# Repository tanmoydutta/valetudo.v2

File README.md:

# Valetudo V2 - a CR2032 powered Temperature and Humidity sensor with ePaper display
Valetudo V2 has been an improvement on the previous version to add an onboard SEN40 Temperature / Humidity Sensor. This design also includes adjustments to the Battery circuit as well as support for different variants of the ePaper Display.

The form factor has remained the same for the new PCB and some of the components have been slightly reoriented to make room for the new electronics. Powered by the same CR2032 coin cell with firmware enhancements to improve battery life.

The body and the lid of the enclosure are embedded with magnetic snap-on feature with an acrylic viewing window for protection for the epaper display. 

The enclosure is now fitted with two large 12x3 mm neodymium magnets for better strength to remain stuck with a metallic surface like a refrigerator or a whiteboard.

This project is certified as Open Source Hardware - 
<p align="center">
  
</p>

License information on the hardware and software and documentation is as follows -

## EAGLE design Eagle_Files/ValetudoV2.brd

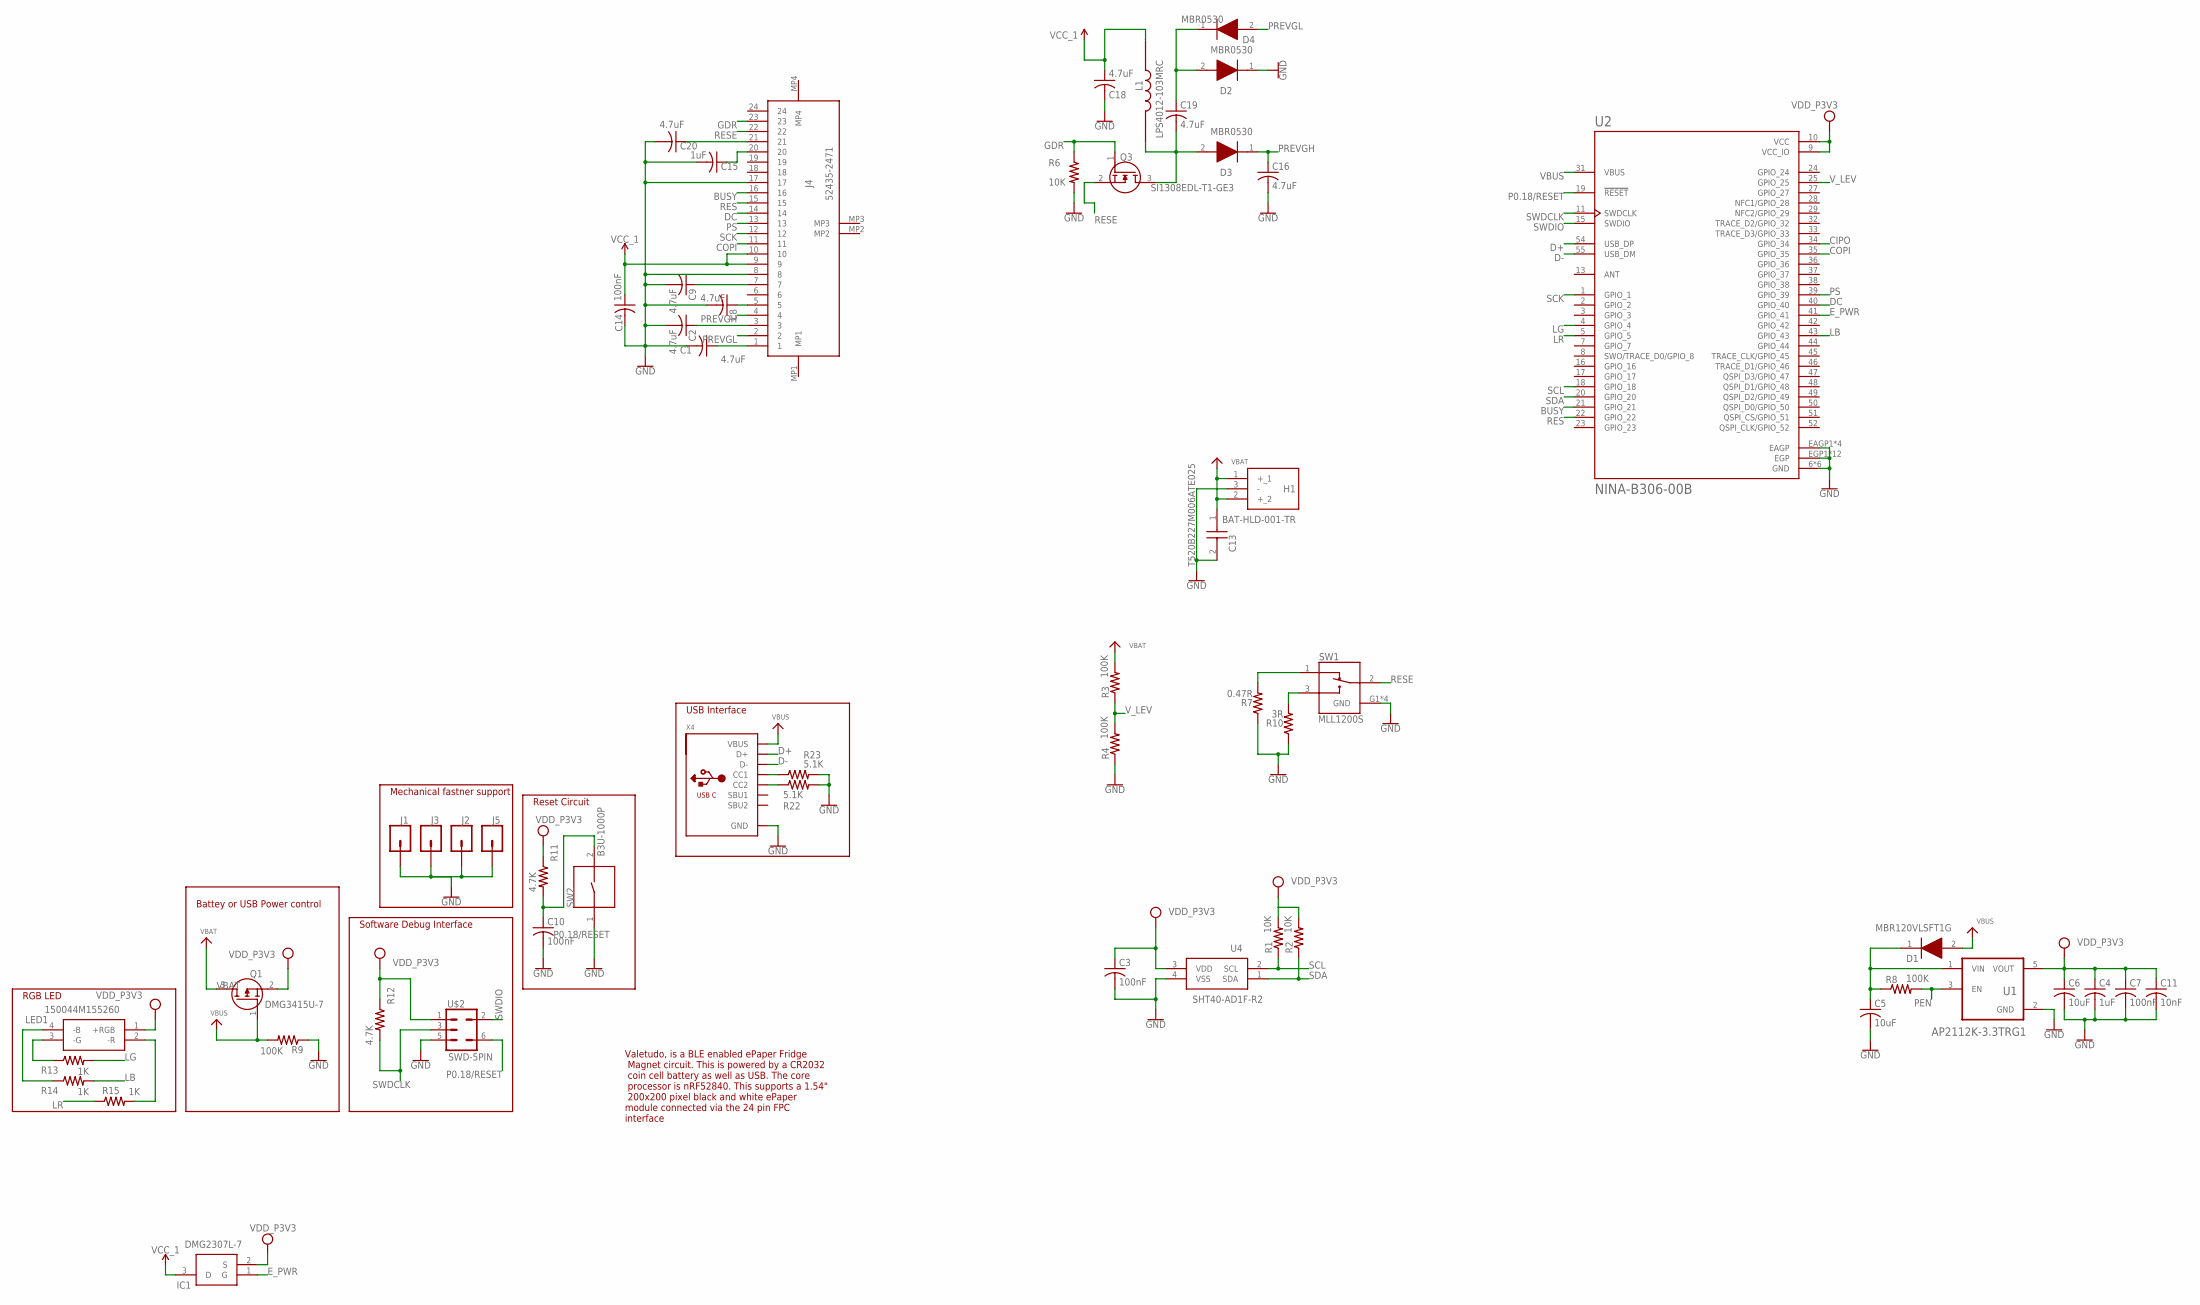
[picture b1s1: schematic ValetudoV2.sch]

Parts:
C1, C2, C8, C9, C16, C18, C19, C20: 4.7uF; C0402
C3, C7, C10, C14: 100nF; C0402
C4, C15: 1uF; C0402
C5, C6: 10uF; C0402
C11: 10nF; C0402
C13: T520B227M006ATE025; T520B
D1: MBR120VLSFT1G; SODFL3616X98N
D2, D3, D4: MBR0530; SOD3716X135N
H1: BAT-HLD-001-TR; BATHLD001TR
IC1: DMG2307L-7; SOT96P240X110-3N
J1, J2, J3, J5: CONN_01PTH_2MM; 1X01_2MM
J4: 52435-2471; 524352471
L1: LPS4012-103MRC; IND_LPS4012-103MRC
LED1: 150044M155260
Q1: DMG3415U-7; SOT96P240X100-3N
Q3: SI1308EDL-T1-GE3; SOT65P210X110-3N
R1, R2, R6: 10K; R0402
R3, R4, R8, R9: 100K; R0402
R7: 0.47R; R0402
R10: 3R; R0402
R11, R12: 4.7K; R0402
R13, R14, R15: 1K; R0402
R22, R23: 5.1K; R0402
SW1: MLL1200S; SW_MLL1200S
SW2: B3U-1000P; SW_B3U-1000P
U1: AP2112K-3.3TRG1; SOT95P285X140-5N
U2: NINA-B306-00B; XCVR_NINA-B306-00B
U4: SHT40-AD1F-R2; SHT40AD1FR2
U$2: SWD-5PIN; PAD_05_03X2_TP_NO4
X4: MICROBUILDER_USB_C; MICROBUILDER_USB_C_CUSB31-CFM2AX-01-X

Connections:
BUSY: J4.16, U2.21 (GPIO_21)
CIPO: U2.34 (GPIO_34)
COPI: J4.11, U2.35 (GPIO_35)
D+: U2.54 (USB_DP), X4.A6 (D+), X4.B6 (D+)
D-: U2.55 (USB_DM), X4.A7 (D-), X4.B7 (D-)
DC: J4.14, U2.40 (GPIO_40)
E_PWR: IC1.1 (G), U2.41 (GPIO_41)
GDR: J4.23, Q3.1 (G), R6.1
GND: C1.2, C2.2, C3.2, C4.2, C5.2, C6.2, C7.2, C8.2, C9.2, C10.2, C11.2, C13.2 (-), C14.2, C15.2, C16.2, C18.2, C20.2, D2.1 (K), H1.3 (-), J1.1, J2.1, J3.1, J4.8, J4.17, J5.1, R4.1, R6.2, R7.1, R9.1, R10.1, R22.2, R23.2, SW1.G1 (GND), SW1.G2 (GND), SW1.G3 (GND), SW1.G4 (GND), SW2.1, U1.2 (GND), U2.6 (GND), U2.12 (GND), U2.14 (GND), U2.26 (GND), U2.30 (GND), U2.53 (GND), U2.EAGP1 (EAGP), U2.EAGP2 (EAGP), U2.EAGP3 (EAGP), U2.EAGP4 (EAGP), U2.EGP1 (EGP), U2.EGP2 (EGP), U2.EGP3 (EGP), U2.EGP4 (EGP), U2.EGP5 (EGP), U2.EGP6 (EGP), U2.EGP7 (EGP), U2.EGP8 (EGP), U2.EGP9 (EGP), U2.EGP10 (EGP), U2.EGP11 (EGP), U2.EGP12 (EGP), U4.4 (VSS), U$2.5, X4.A1B12 (GND), X4.B1A12 (GND)
LB: R14.2, U2.43 (GPIO_43)
LG: R13.2, U2.4 (GPIO_4)
LR: R15.1, U2.5 (GPIO_5)
unnamed: LED1.4 (-B), R14.1
unnamed: LED1.3 (-G), R13.1
unnamed: LED1.2 (-R), R15.2
unnamed: R7.2, SW1.1
unnamed: C1.1, J4.1
unnamed: C19.1, D2.2 (A), D4.1 (K)
unnamed: R22.1, X4.B5 (CC2)
unnamed: C2.1, J4.3
unnamed: R23.1, X4.A5 (CC1)
unnamed: C5.1, D1.1 (K), R8.1, U1.1 (VIN)
unnamed: C19.2, D3.2 (A), L1.2, Q3.3 (D)
unnamed: C8.1, J4.5
unnamed: R10.2, SW1.3
unnamed: C9.1, J4.7
unnamed: C15.1, J4.20
unnamed: C20.1, J4.21
P0.18/RESET: C10.1, R11.2, SW2.2, U2.19 (!RESET), U$2.6
PEN: R8.2, U1.3 (EN)
PREVGH: C16.1, D3.1 (K), J4.4
PREVGL: D4.2 (A), J4.2
PS: J4.13, U2.39 (GPIO_39)
RES: J4.15, U2.22 (GPIO_22)
RESE: J4.22, Q3.2 (S), SW1.2
SCK: J4.12, U2.1 (GPIO_1)
SCL: R1.1, U2.18 (GPIO_18), U4.2 (SCL)
SDA: R2.1, U2.20 (GPIO_20), U4.1 (SDA)
SWDCLK: R12.2, U2.11 (SWDCLK), U$2.3
SWDIO: U2.15 (SWDIO), U$2.2
VBAT: C13.1 (+), H1.1 (+_1), H1.2 (+_2), Q1.3 (D), R3.2
VBUS: D1.2 (A), Q1.1 (G), R9.2, U2.31 (VBUS), X4.A4B9 (VBUS), X4.B4A9 (VBUS)
VCC: C3.1, C4.1, C6.1, C7.1, C11.1, IC1.2 (S), LED1.1 (+RGB), Q1.2 (S), R1.2, R2.2, R11.1, R12.1, U1.5 (VOUT), U2.9 (VCC_IO), U2.10 (VCC), U4.3 (VDD), U$2.1
VCC_1: C14.1, C18.1, IC1.3 (D), J4.9, J4.10, L1.1
V_LEV: R3.1, R4.2, U2.25 (GPIO_25)

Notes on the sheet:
Battey or USB Power control
Reset Circuit
USB Interface
Software Debug Interface
Valetudo, is a BLE enabled ePaper Fridge Magnet circuit. This is powered by a CR2032 coin cell battery as well as USB. The core processor is nRF52840. This supports a 1.54" 200x200 pixel black and white ePaper module connected via the 24 pin FPC interface
RGB LED
Mechanical fastner support

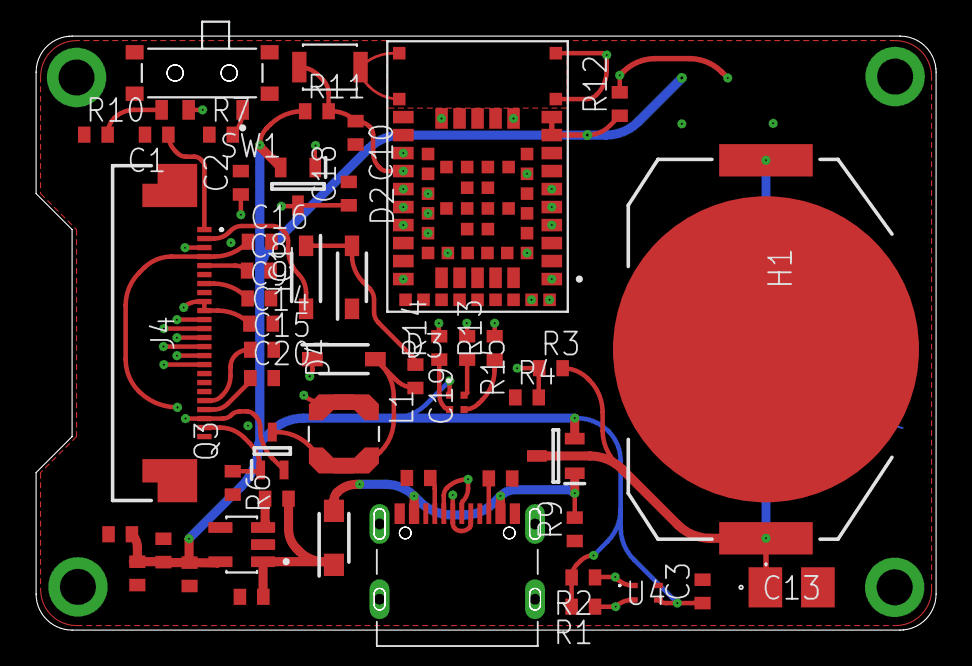
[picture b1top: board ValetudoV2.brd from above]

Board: 6 copper layers, 50.0 x 33.0 mm, 56 parts (1 on the bottom side), 44 nets.

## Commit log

2025-09-03 Adding structure
2025-09-03 Added 3D files documentation and images
2025-09-03 Added schematics
2025-09-03 Adding images to readme
2025-09-04 Adding some more images
2025-09-11 Adding another image
2025-09-11 Update README.md
    Adding more information on the new version of the design
2025-09-11 Adding source code for the sample program
2025-09-13 Adding License Information
2025-09-16 Update README.md
    Documentation update
2025-09-20 Adding OSHWA mark image
2025-09-20 Update README.md
    Adding OSHWA mark
2025-09-20 Update README.md
    Update OSHWA link
2025-09-20 Update README.md
    Updte documentation

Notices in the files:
parts and their libraries:
SparkFun-Connectors: Licensing: Creative Commons ShareAlike 4.0 International - https://creativecommons.org/licenses/by-sa/4.0
